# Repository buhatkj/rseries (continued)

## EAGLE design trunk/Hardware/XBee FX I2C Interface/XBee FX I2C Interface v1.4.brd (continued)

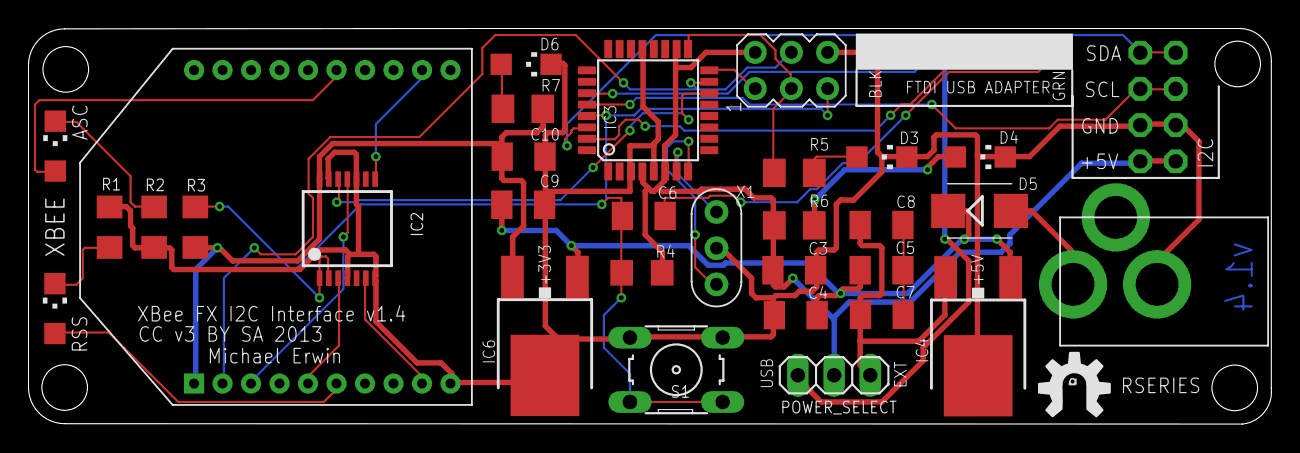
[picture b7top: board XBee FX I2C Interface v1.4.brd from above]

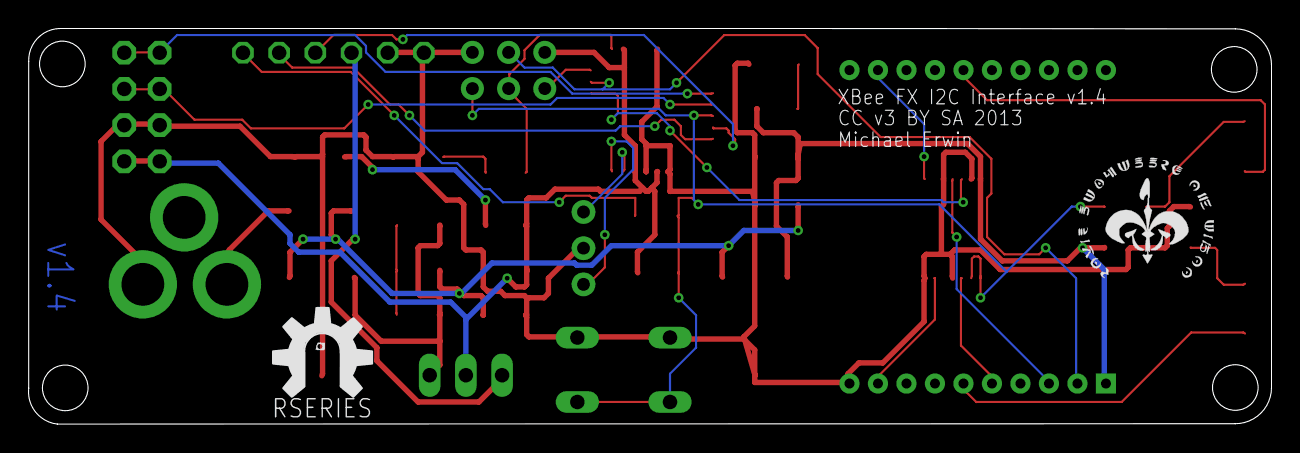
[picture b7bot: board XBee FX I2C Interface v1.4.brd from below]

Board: 2 copper layers, 87.2 x 27.8 mm, 37 parts (2 on the bottom side), 31 nets.

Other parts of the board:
U$2: RSERIES-OSHW-LOGO-LARGE
U$5: ROYAL-ENGINEERS-OF-NABOO-SMALL
